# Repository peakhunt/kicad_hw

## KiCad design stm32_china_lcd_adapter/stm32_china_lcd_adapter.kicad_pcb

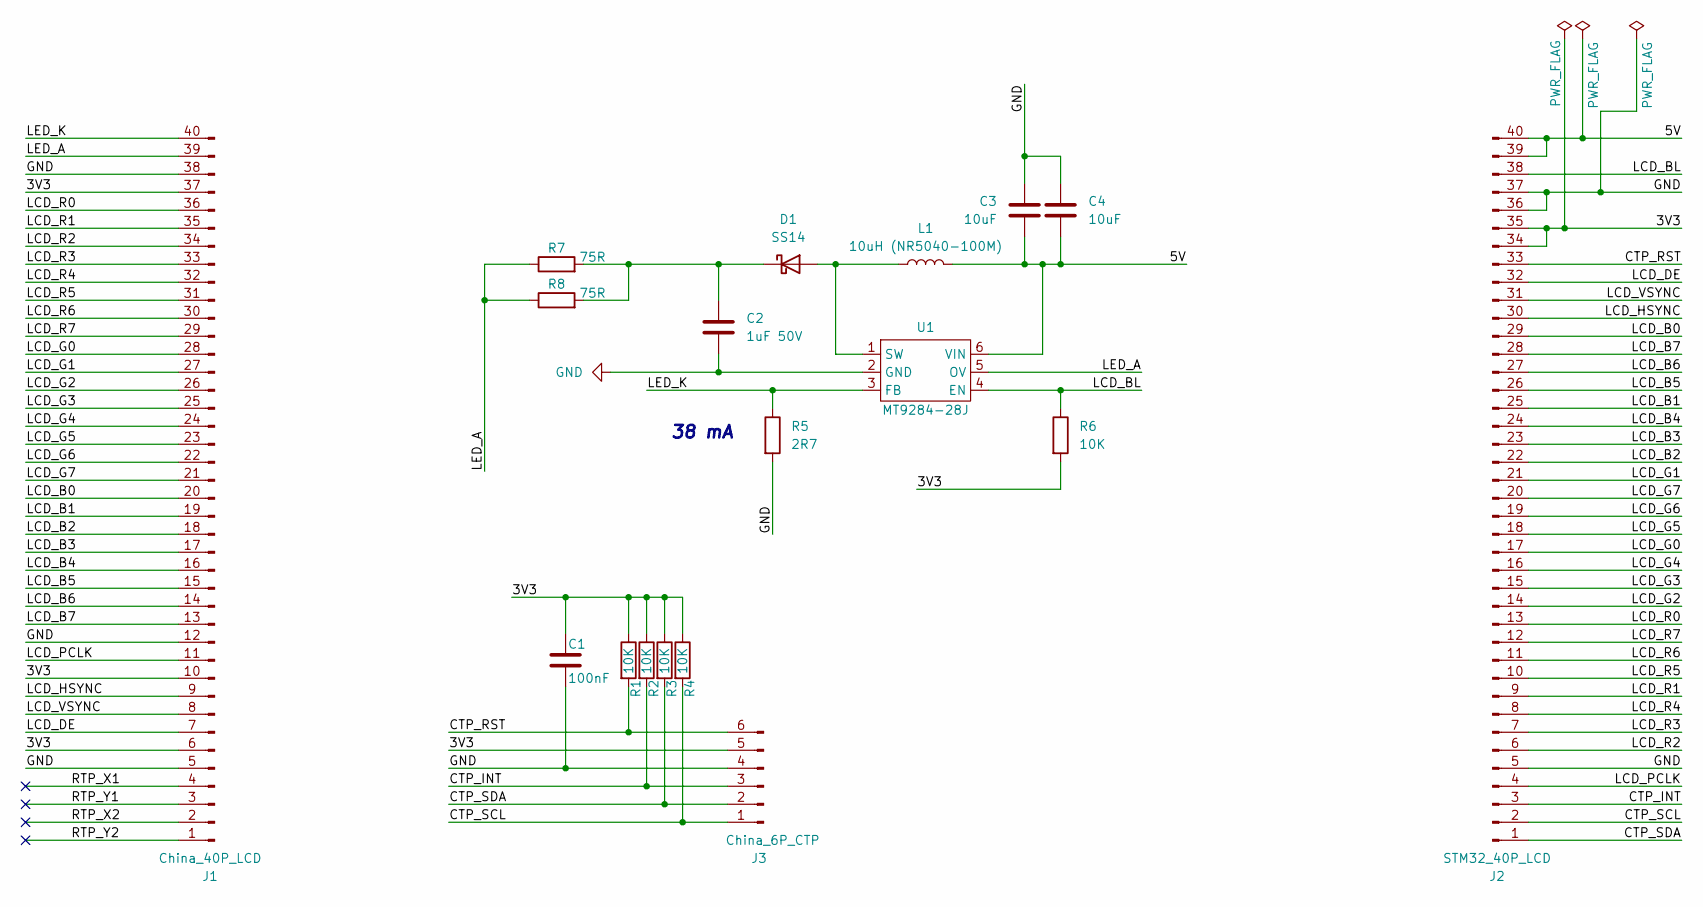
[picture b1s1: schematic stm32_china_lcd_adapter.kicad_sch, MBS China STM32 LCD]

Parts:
C1: 100nF; C_0603_1608Metric
C2: 1uF 50V; C_0603_1608Metric
C3, C4: 10uF; C_0603_1608Metric
D1: SS14; D_SMA
J1: China_40P_LCD; TE_4-1734839-0_1x40-1MP_P0.5mm_Horizontal
J2: STM32_40P_LCD; TE_4-1734839-0_1x40-1MP_P0.5mm_Horizontal
J3: China_6P_CTP; Hirose_FH12-6S-0.5SH_1x06-1MP_P0.50mm_Horizontal
L1: 10uH (NR5040-100M); L_Wuerth_HCI-5040
R1, R2, R3, R4, R6: 10K; R_0603_1608Metric
R5: 2R7; R_0603_1608Metric
R7, R8: 75R; R_0603_1608Metric
U1: MT9284-28J; SOT-23-6

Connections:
/3V3: C1.1, J1.6, J1.10, J1.37, J2.34, J2.35, J3.5, R1.1, R2.1, R3.1, R4.1, R6.2
/5V: C3.2, C4.2, J2.39, J2.40, L1.2, U1.6 (VIN)
/CTP_INT: J2.3, J3.3, R2.2
/CTP_RST: J2.33, J3.6, R1.2
/CTP_SCL: J2.2, J3.1, R4.2
/CTP_SDA: J2.1, J3.2, R3.2
/LCD_B0: J1.20, J2.29
/LCD_B1: J1.19, J2.25
/LCD_B2: J1.18, J2.22
/LCD_B3: J1.17, J2.23
/LCD_B4: J1.16, J2.24
/LCD_B5: J1.15, J2.26
/LCD_B6: J1.14, J2.27
/LCD_B7: J1.13, J2.28
/LCD_BL: J2.38, R6.1, U1.4 (EN)
/LCD_DE: J1.7, J2.32
/LCD_G0: J1.28, J2.17
/LCD_G1: J1.27, J2.21
/LCD_G2: J1.26, J2.14
/LCD_G3: J1.25, J2.15
/LCD_G4: J1.24, J2.16
/LCD_G5: J1.23, J2.18
/LCD_G6: J1.22, J2.19
/LCD_G7: J1.21, J2.20
/LCD_HSYNC: J1.9, J2.30
/LCD_PCLK: J1.11, J2.4
/LCD_R0: J1.36, J2.13
/LCD_R1: J1.35, J2.9
/LCD_R2: J1.34, J2.6
/LCD_R3: J1.33, J2.7
/LCD_R4: J1.32, J2.8
/LCD_R5: J1.31, J2.10
/LCD_R6: J1.30, J2.11
/LCD_R7: J1.29, J2.12
/LCD_VSYNC: J1.8, J2.31
/LED_A: J1.39, R7.1, R8.1, U1.5 (OV)
/LED_K: J1.40, R5.1, U1.3 (FB)
/RTP_X1: J1.4
/RTP_X2: J1.2
/RTP_Y1: J1.3
/RTP_Y2: J1.1
GND: C1.2, C2.2, C3.1, C4.1, J1.5, J1.12, J1.38, J2.5, J2.36, J2.37, J3.4, R5.2, U1.2 (GND)
unnamed: D1.2 (A), L1.1, U1.1 (SW)
unnamed: C2.1, D1.1 (K), R7.2, R8.2

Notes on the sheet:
38 mA

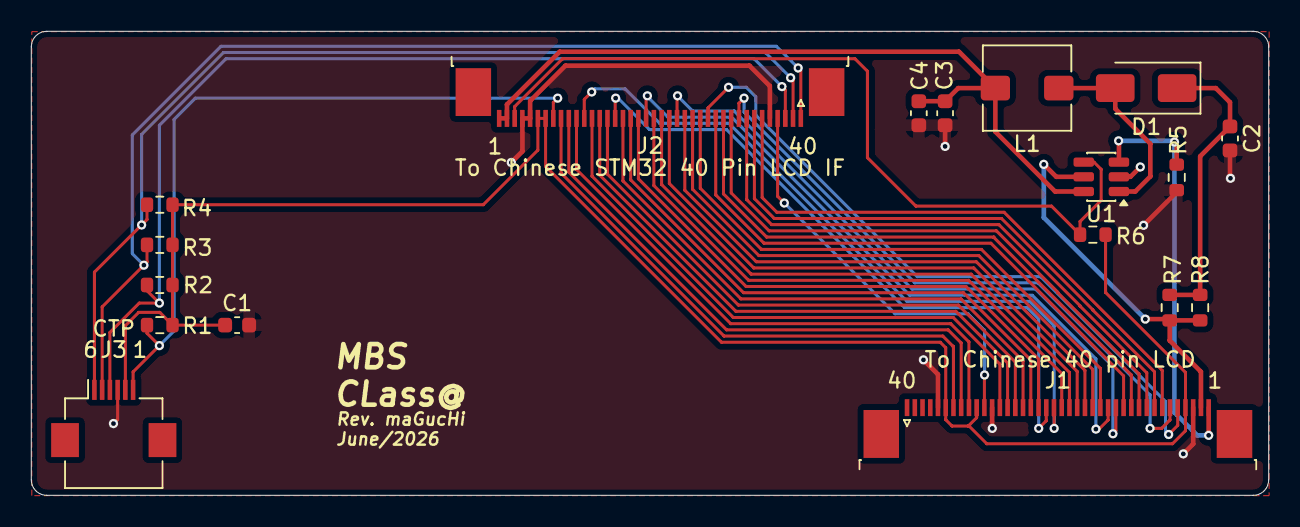
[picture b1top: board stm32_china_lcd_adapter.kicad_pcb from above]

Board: 2 copper layers, 80.0 x 30.0 mm, 18 parts (0 on the bottom side), 40 nets.

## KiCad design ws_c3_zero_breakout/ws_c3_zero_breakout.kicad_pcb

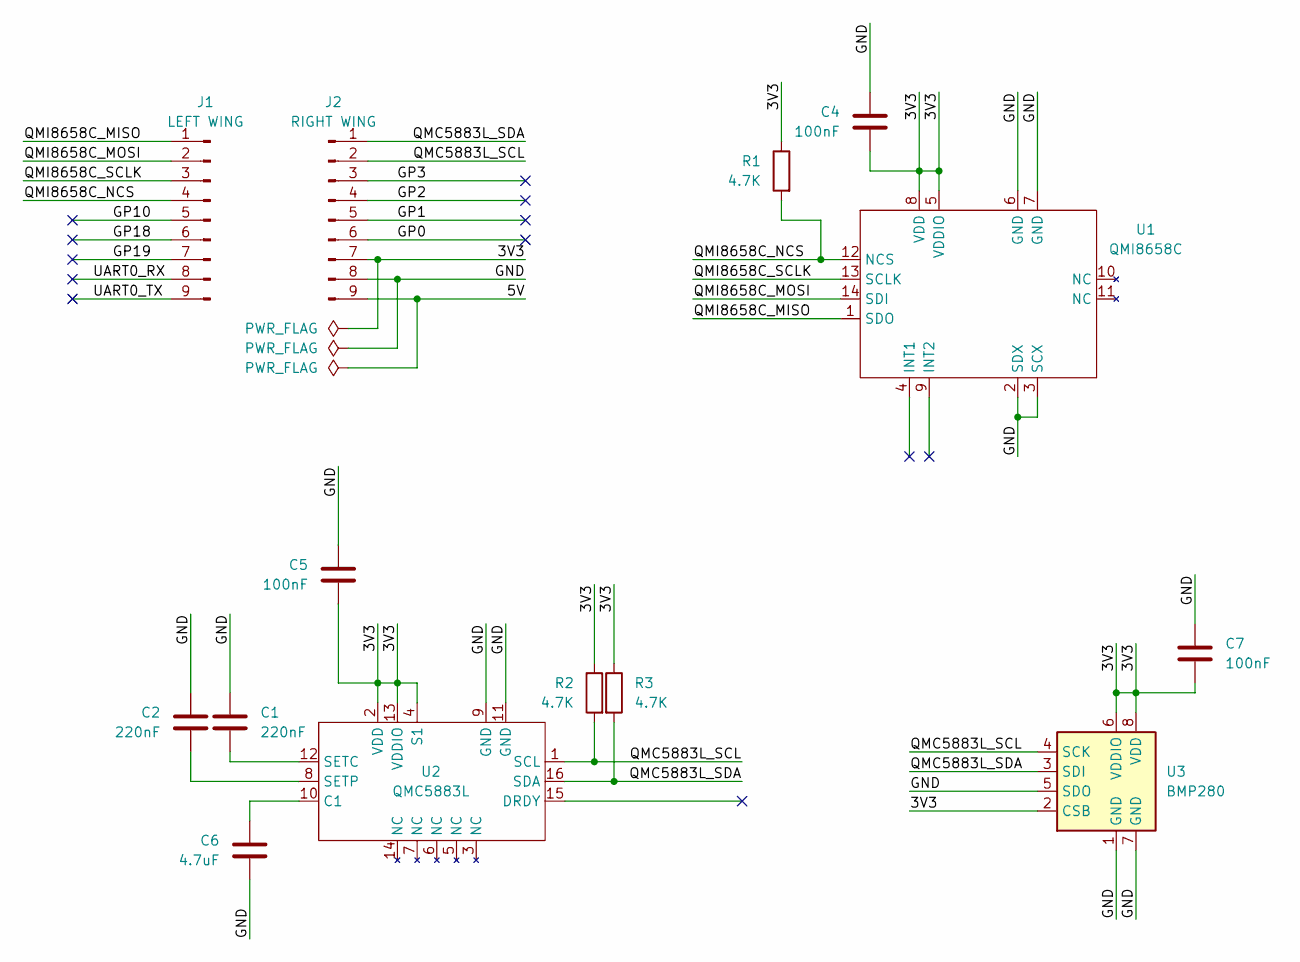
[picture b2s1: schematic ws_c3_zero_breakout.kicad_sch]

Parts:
C1, C2: 220nF; C_0603_1608Metric
C4, C5, C7: 100nF; C_0603_1608Metric
C6: 4.7uF; C_0603_1608Metric
J1: LEFT WING; PinHeader_1x09_P2.54mm_Vertical
J2: RIGHT WING; PinHeader_1x09_P2.54mm_Vertical
R1, R2, R3: 4.7K; R_0603_1608Metric
U1: QMI8658C; Bosch_LGA-14_3x2.5mm_P0.5mm
U2: QMC5883L; LGA-16_3x3mm_P0.5mm
U3: BMP280; Bosch_LGA-8_2x2.5mm_P0.65mm_ClockwisePinNumbering

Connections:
/3V3: C4.2, C5.2, C7.2, J2.7, R1.1, R2.1, R3.1, U1.5 (VDDIO), U1.8 (VDD), U2.2 (VDD), U2.4 (S1), U2.13 (VDDIO), U3.2 (CSB), U3.6 (VDDIO), U3.8 (VDD)
/5V: J2.9
/ GP0: J2.6
/GND: C1.1, C2.1, C4.1, C5.1, C6.2, C7.1, J2.8, U1.2 (SDX), U1.3 (SCX), U1.6 (GND), U1.7 (GND), U2.9 (GND), U2.11 (GND), U3.1 (GND), U3.5 (SDO), U3.7 (GND)
/GP1: J2.5
/GP2: J2.4
/GP3: J2.3
/GP10: J1.5
/GP18: J1.6
/GP19: J1.7
/QMC5883L_SCL: J2.2, R2.2, U2.1 (SCL), U3.4 (SCK)
/QMC5883L_SDA: J2.1, R3.2, U2.16 (SDA), U3.3 (SDI)
/QMI8658C_MISO: J1.1, U1.1 (SDO)
/QMI8658C_MOSI: J1.2, U1.14 (SDI)
/QMI8658C_NCS: J1.4, R1.2, U1.12 (NCS)
/QMI8658C_SCLK: J1.3, U1.13 (SCLK)
/UART0_RX: J1.8
/UART0_TX: J1.9
unnamed: C6.1, U2.10 (C1)
unnamed: C1.2, U2.12 (SETC)
unnamed: C2.2, U2.8 (SETP)

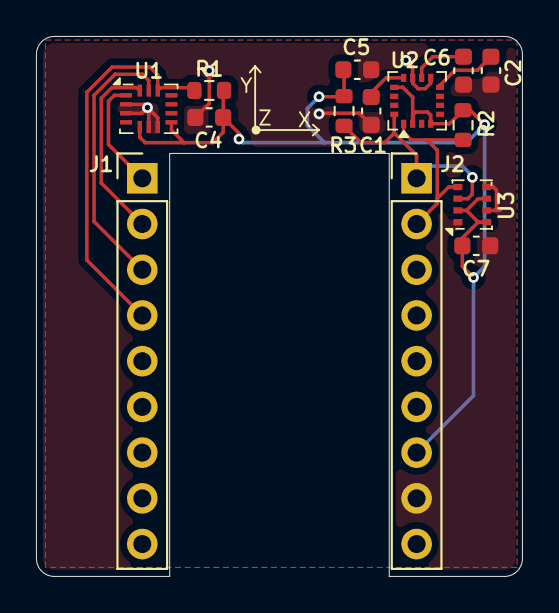
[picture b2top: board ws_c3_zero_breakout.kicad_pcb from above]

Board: 2 copper layers, 27.0 x 30.0 mm, 14 parts (0 on the bottom side), 11 nets.

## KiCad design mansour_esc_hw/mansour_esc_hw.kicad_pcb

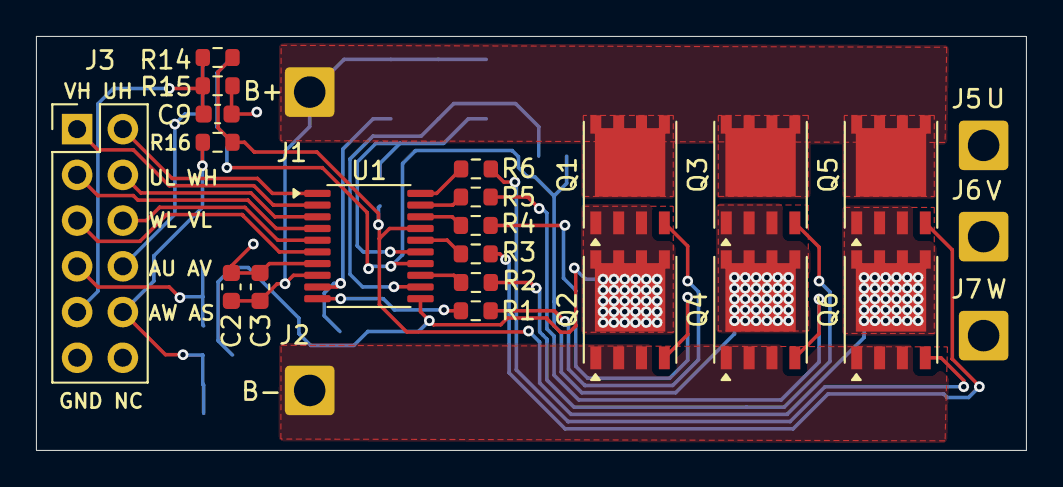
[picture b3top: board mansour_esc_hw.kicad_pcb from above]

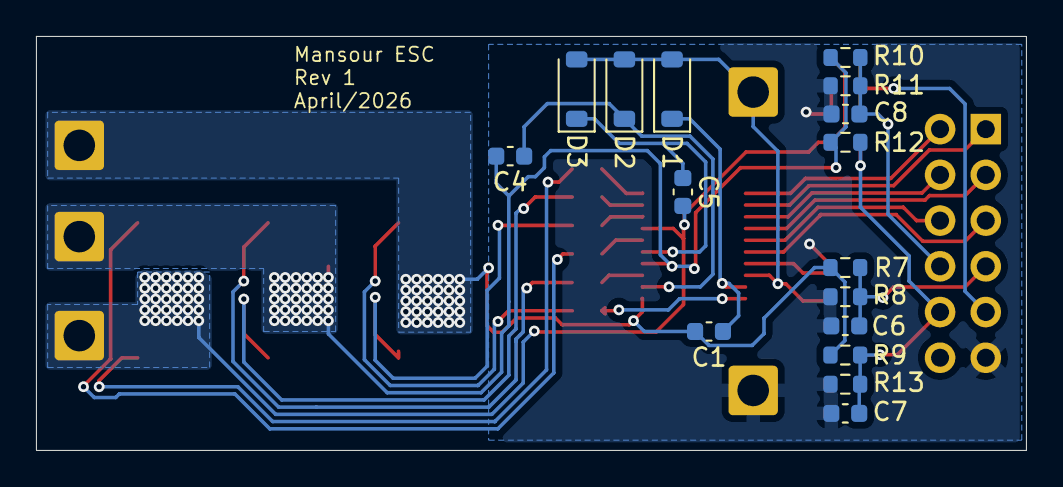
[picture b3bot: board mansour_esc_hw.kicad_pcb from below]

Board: 2 copper layers, 55.0 x 23.0 mm, 41 parts (16 on the bottom side), 30 nets.

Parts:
C1, C2, C4, C5: 1uF; C_0603_1608Metric
C3: 10uF; C_0603_1608Metric
C6, C7, C8, C9: 100pF; C_0603_1608Metric
D1, D2, D3: 1N4148W; D_SOD-123
J1: B+; SolderWire-1sqmm_1x01_D1.4mm_OD2.7mm
J2: B-; SolderWire-1sqmm_1x01_D1.4mm_OD2.7mm
J3: uC connect; PinHeader_2x06_P2.54mm_Vertical
J5: Motor U; SolderWire-1sqmm_1x01_D1.4mm_OD2.7mm
J6: Motor V; SolderWire-1sqmm_1x01_D1.4mm_OD2.7mm
J7: Motor W; SolderWire-1sqmm_1x01_D1.4mm_OD2.7mm
Q1, Q2, Q3, Q4, Q5, Q6: AON6414A; PowerPAK_SO-8_Single
R1, R2, R3, R4, R5, R6: 10; R_0603_1608Metric
R7, R9, R10, R12, R14, R16: 47K; R_0603_1608Metric
R8, R11, R15: 10K; R_0603_1608Metric
R13: 3.3K; R_0603_1608Metric
U1: FD6288T; TSSOP-20_4.4x6.5mm_P0.65mm

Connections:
/ADC_STAR: C7.2, J3.10, R9.2, R12.2, R13.1, R16.2
/ADC_U: C6.2, J3.7, R7.2, R8.1
/ADC_V: C8.2, J3.8, R10.2, R11.1
/ADC_W: C9.2, J3.9, R14.2, R15.1
/PHASE_U: C1.2, J5.1 (Pin_1_1), Q1.1 (S), Q1.2 (S), Q1.3 (S), Q2.5 (D), R7.1, R9.1, U1.11 (VS1)
/PHASE_V: C4.2, J6.1 (Pin_1_1), Q3.1 (S), Q3.2 (S), Q3.3 (S), Q4.5 (D), R10.1, R12.1, U1.14 (VS2)
/PHASE_W: C5.2, J7.1 (Pin_1_1), Q5.1 (S), Q5.2 (S), Q5.3 (S), Q6.5 (D), R14.1, R16.1, U1.17 (VS3)
/U_H: J3.2, U1.1 (HIN1)
/U_HS: Q1.4 (G), R1.2
/U_L: J3.3, U1.4 (LIN1)
/U_LS: Q2.4 (G), R4.2
/VBUS: C2.1, C3.1, D1.2 (A), D2.2 (A), D3.2 (A), J1.1 (Pin_1_1), Q1.5 (D), Q3.5 (D), Q5.5 (D), U1.8 (VCC)
/V_H: J3.1, U1.2 (HIN2)
/V_HS: Q3.4 (G), R2.2
/V_L: J3.6, U1.5 (LIN2)
/V_LS: Q4.4 (G), R5.2
/W_H: J3.4, U1.3 (HIN3)
/W_HS: Q5.4 (G), R3.2
/W_L: J3.5, U1.6 (LIN3)
/W_LS: Q6.4 (G), R6.2
GND: C2.2, C3.2, C6.1, C7.1, C8.1, C9.1, J2.1 (Pin_1_1), J3.11, Q2.1 (S), Q2.2 (S), Q2.3 (S), Q4.1 (S), Q4.2 (S), Q4.3 (S), Q6.1 (S), Q6.2 (S), Q6.3 (S), R8.2, R11.2, R13.2, R15.2, U1.7 (VSS)
unnamed: C1.1, D1.1 (K), U1.9 (VB1)
unnamed: C4.1, D2.1 (K), U1.12 (VB2)
unnamed: C5.1, D3.1 (K), U1.15 (VB3)
unnamed: R1.1, U1.10 (HO1)
unnamed: R2.1, U1.13 (HO2)
unnamed: R3.1, U1.16 (HO3)
unnamed: R4.1, U1.18 (LO1)
unnamed: R5.1, U1.19 (LO2)
unnamed: R6.1, U1.20 (LO3)

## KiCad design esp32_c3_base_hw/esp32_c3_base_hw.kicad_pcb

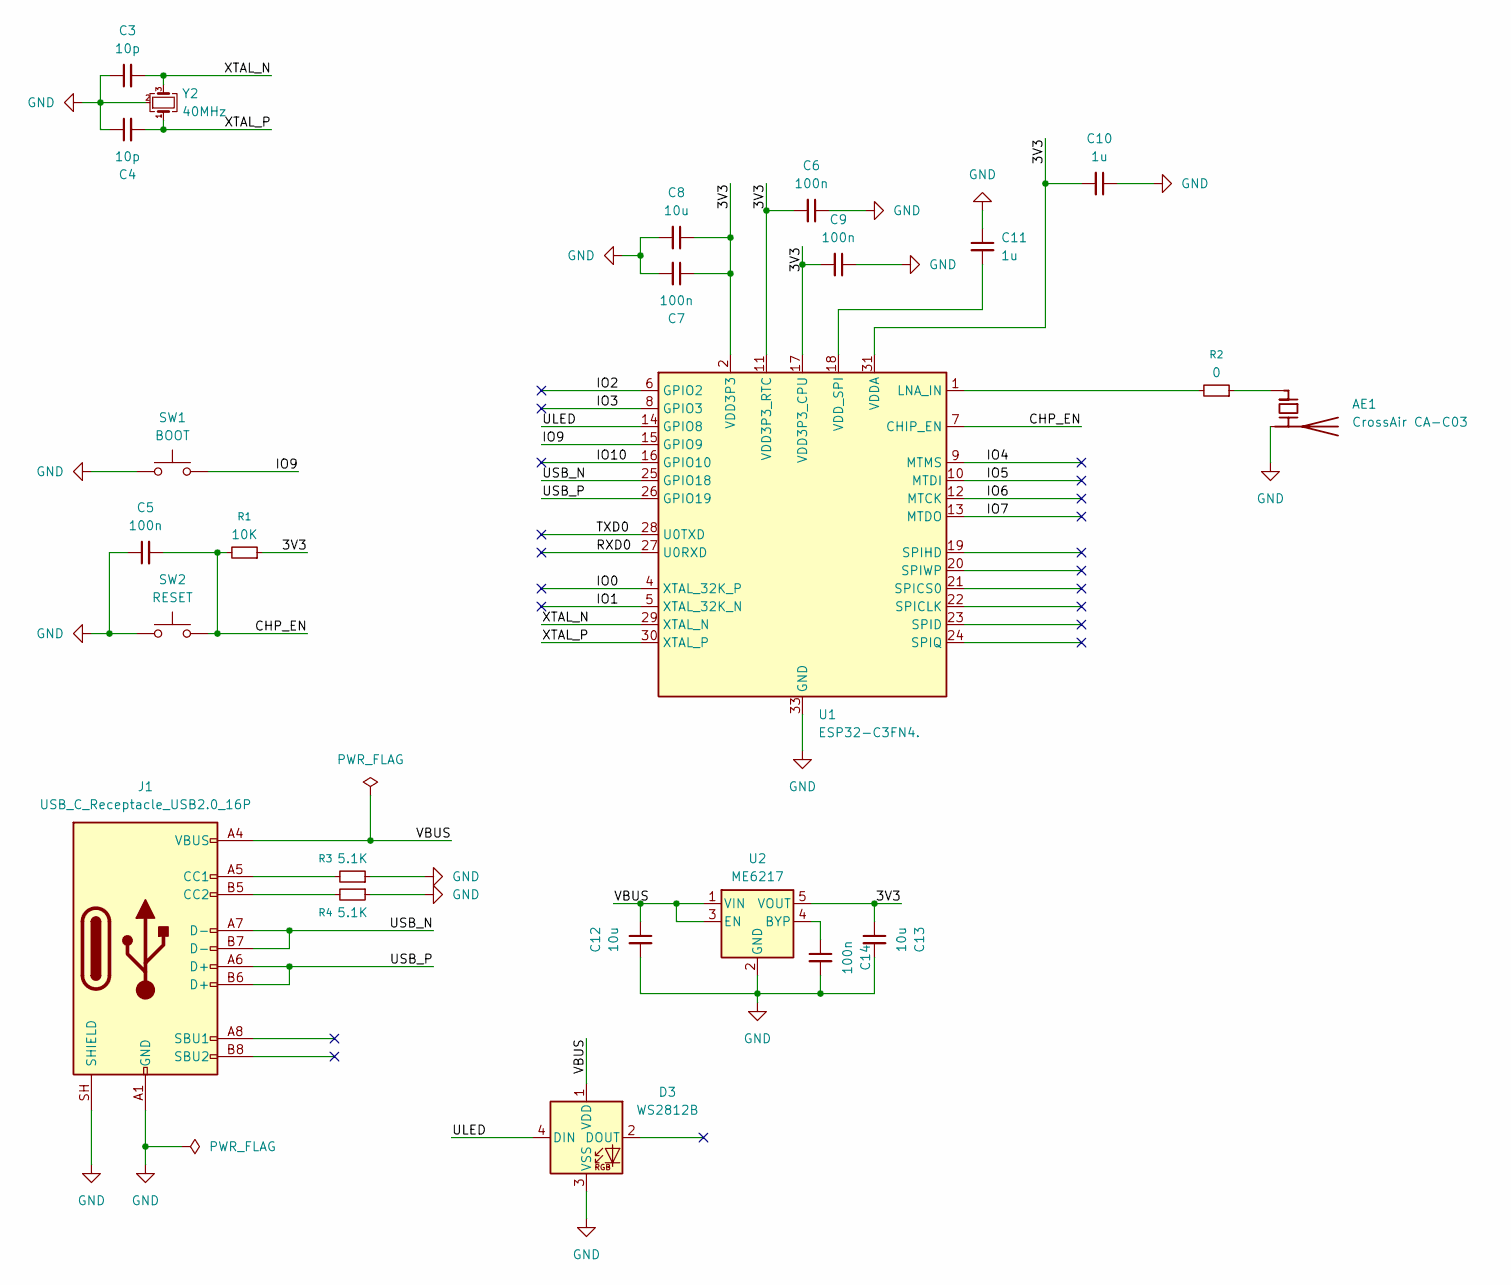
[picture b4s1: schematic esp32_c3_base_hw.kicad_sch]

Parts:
AE1: CrossAir CA-C03; CA-C03_Antenna
C3, C4: 10p; C_0402_1005Metric
C5, C6, C7, C9, C14: 100n; C_0402_1005Metric
C8, C12, C13: 10u; C_0402_1005Metric
C10, C11: 1u; C_0402_1005Metric
D3: WS2812B; LED_WS2812B-2020_PLCC4_2.0x2.0mm
J1: USB_C_Receptacle_USB2.0_16P; USB_C_Receptacle_HRO_TYPE-C-31-M-12
R1: 10K; R_0402_1005Metric
R2: 0; R_0402_1005Metric
R3, R4: 5.1K; R_0402_1005Metric
SW1: BOOT; SW_SPST_PTS810
SW2: RESET; SW_SPST_PTS810
U1: ESP32-C3FN4.; QFN-32-1EP_5x5mm_P0.5mm_EP3.7x3.7mm
U2: ME6217; SOT-23-5
Y2: 40MHz; Crystal_SMD_3225-4Pin_3.2x2.5mm

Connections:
/3V3: C6.2, C7.1, C8.1, C9.2, C10.2, C13.1, R1.1, U1.2 (VDD3P3), U1.3 (VDD3P3), U1.11 (VDD3P3_RTC), U1.17 (VDD3P3_CPU), U1.31 (VDDA), U1.32 (VDDA), U2.5 (VOUT)
/CHP_EN: C5.2, R1.2, SW2.2, U1.7 (CHIP_EN)
/IO0: U1.4 (XTAL_32K_P)
/IO1: U1.5 (XTAL_32K_N)
/IO2: U1.6 (GPIO2)
/IO3: U1.8 (GPIO3)
/IO4: U1.9 (MTMS)
/IO5: U1.10 (MTDI)
/IO6: U1.12 (MTCK)
/IO7: U1.13 (MTDO)
/IO9: SW1.2, U1.15 (GPIO9)
/IO10: U1.16 (GPIO10)
/RXD0: U1.27 (U0RXD)
/TXD0: U1.28 (U0TXD)
/ULED: D3.4 (DIN), U1.14 (GPIO8)
/USB_N: J1.A7 (D-), J1.B7 (D-), U1.25 (GPIO18)
/USB_P: J1.A6 (D+), J1.B6 (D+), U1.26 (GPIO19)
/VBUS: C12.1, D3.1 (VDD), J1.A4 (VBUS), J1.A9 (VBUS), J1.B4 (VBUS), J1.B9 (VBUS), U2.1 (VIN), U2.3 (EN)
/XTAL_N: C3.2, U1.29 (XTAL_N), Y2.3
/XTAL_P: C4.2, U1.30 (XTAL_P), Y2.1
GND: AE1.2 (PCB_Trace), C3.1, C4.1, C5.1, C6.1, C7.2, C8.2, C9.1, C10.1, C11.1, C12.2, C13.2, C14.2, D3.3 (VSS), J1.A1 (GND), J1.A12 (GND), J1.B1 (GND), J1.B12 (GND), J1.SH (SHIELD), R3.1, R4.1, SW1.1, SW2.1, U1.33 (GND), U2.2 (GND), Y2.2 (G), Y2.4 (G)
unnamed: AE1.1 (FEED), R2.1
unnamed: J1.A5 (CC1), R3.2
unnamed: J1.B5 (CC2), R4.2
unnamed: R2.2, U1.1 (LNA_IN)
unnamed: C11.2, U1.18 (VDD_SPI)
unnamed: C14.1, U2.4 (BYP)

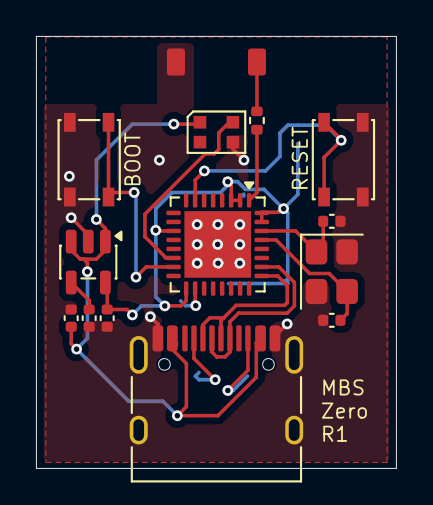
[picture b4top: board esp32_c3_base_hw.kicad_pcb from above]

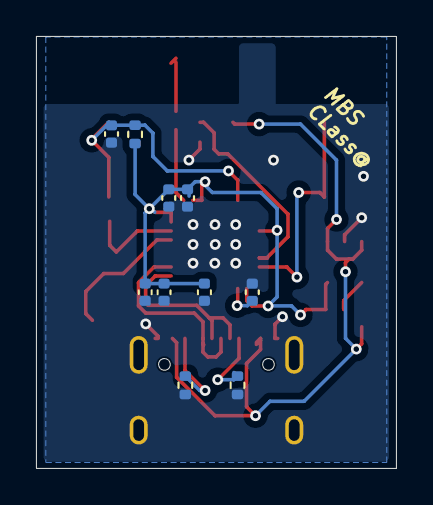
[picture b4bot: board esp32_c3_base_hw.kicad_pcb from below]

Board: 2 copper layers, 20.0 x 24.0 mm, 24 parts (10 on the bottom side), 16 nets.

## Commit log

2026-04-20 initial import
2026-04-20 Create LICENSE
2026-04-21 adding comments
2026-04-22 working on waveshare esp32c3 zero board breakout module
2026-04-22 silkscreen alignment
2026-04-22 comment and label change
2026-04-22 board edgecut fix
2026-04-23 fixing major pin map bug in symbol
2026-04-23 adding bmp280
2026-04-23 cleanup
2026-05-06 adding chinese stm32 to chinese 40p standard lcd panel adapter board
2026-05-07 adding dumb passive lcd adapter for wildfire and stm32h7 chinese board
2026-05-07 fixing pinout error from wrong manual
2026-05-07 fixing fucking flipped fpc connector. how stupid of me!
2026-05-18 adding cyclone10 ez-usb adapter
2026-05-31 upgradinng lcd adapter with blacklight power
